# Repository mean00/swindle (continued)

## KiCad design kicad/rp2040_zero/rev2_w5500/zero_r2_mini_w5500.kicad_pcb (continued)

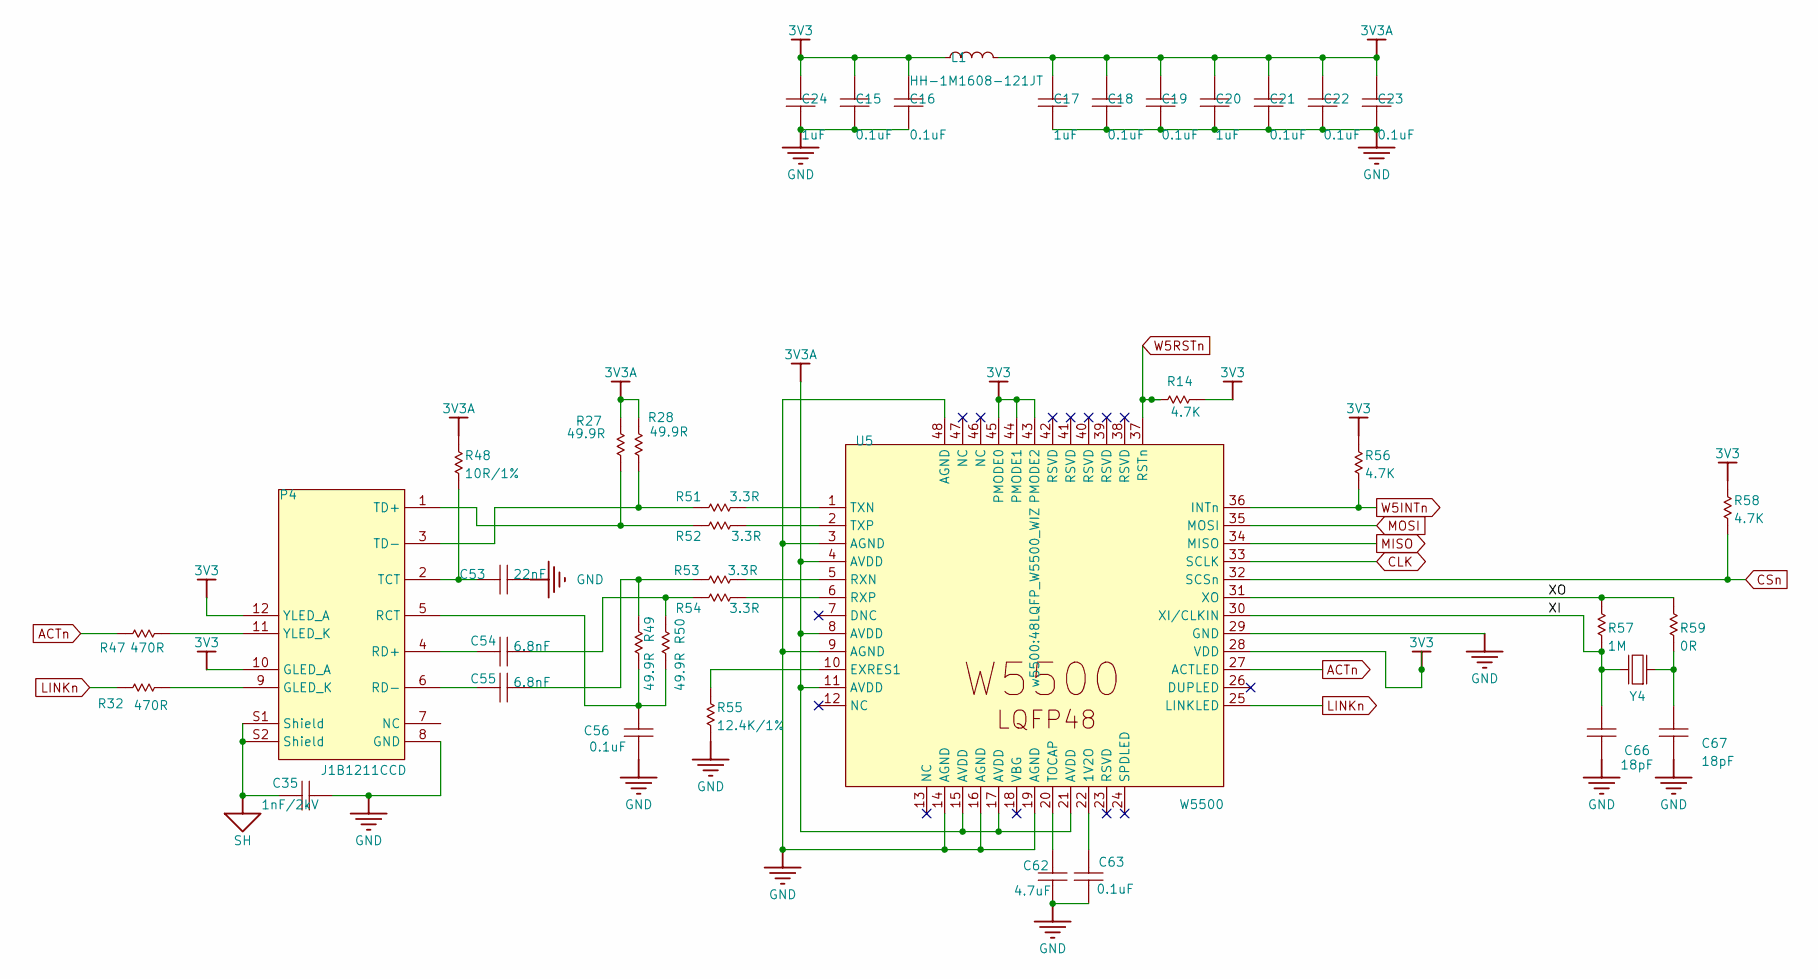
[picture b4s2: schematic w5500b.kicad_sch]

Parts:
C15, C16, C18, C19, C21, C22, C23, C56, C63: 0.1uF; C_0603_1608Metric
C17, C20, C24: 1uF; C_0603_1608Metric
C35: 1nF/2kV; C_0603_1608Metric
C53: 22nF; C_0603_1608Metric
C54, C55: 6.8nF; C_0603_1608Metric
C62: 4.7uF; C_0603_1608Metric
C66, C67: 18pF; C_0603_1608Metric
L1: HH-1M1608-121JT; L_0603_1608Metric
P4: J1B1211CCD; RJ45_Hanrun_HR911105A_Horizontal
R14, R56, R58: 4.7K; R_0603_1608Metric
R27, R28, R49, R50: 49.9R; R_0603_1608Metric
R32, R47: 470R; R_0603_1608Metric
R48: 10R/1%; R_0603_1608Metric
R51, R52, R53, R54: 3.3R; R_0603_1608Metric
R55: 12.4K/1%; R_0603_1608Metric
R57: 1M; R_0603_1608Metric
R59: 0R; R_0603_1608Metric
U5: W5500; 48LQFP_W5500_WIZ
Y4: 25MHz; Crystal_SMD_TXC_7M-4Pin_3.2x2.5mm

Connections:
3V3A: C17.2, C18.2, C19.2, C20.2, C21.2, C22.2, C23.2, L1.2, R27.2, R28.2, R48.1, U5.4 (AVDD), U5.8 (AVDD), U5.11 (AVDD), U5.15 (AVDD), U5.17 (AVDD), U5.21 (AVDD)
+3.3V: C15.2, C16.2, C24.2, L1.1, P4.10 (GLED_A), P4.12 (YLED_A), R14.2, R56.1, R58.1, U5.28 (VDD), U5.43 (PMODE2), U5.44 (PMODE1), U5.45 (PMODE0); also elsewhere on the board
/w5500b/XI: C66.2, R57.1, U5.30 (XI/CLKIN), Y4.1 (inp)
/w5500b/XO: R57.2, R59.2, U5.31 (XO)
ACTn: R47.1, U5.27 (ACTLED)
CLK: U5.33 (SCLK); also elsewhere on the board
CSn: R58.2, U5.32 (SCSn); also elsewhere on the board
GND: C15.1, C16.1, C17.1, C18.1, C19.1, C20.1, C21.1, C22.1, C23.1, C24.1, C35.1, C53.1, C56.1, C62.1, C63.1, C66.1, C67.1, P4.8 (GND), R55.2, U5.3 (AGND), U5.9 (AGND), U5.14 (AGND), U5.16 (AGND), U5.19 (AGND), U5.29 (GND), U5.48 (AGND); also elsewhere on the board
LINKn: R32.1, U5.25 (LINKLED)
MISO: U5.34 (MISO); also elsewhere on the board
MOSI: U5.35 (MOSI); also elsewhere on the board
unnamed: C54.1, R50.2, R54.1
unnamed: C55.1, R49.2, R53.1
unnamed: P4.9 (GLED_K), R32.2
unnamed: C56.2, P4.5 (RCT), R49.1, R50.1
unnamed: C54.2, P4.4 (RD+)
unnamed: C55.2, P4.6 (RD-)
unnamed: C53.2, P4.2 (TCT), R48.2
unnamed: P4.1 (TD+), R27.1, R52.1
unnamed: P4.3 (TD-), R28.1, R51.1
unnamed: P4.11 (YLED_K), R47.2
unnamed: C63.2, U5.22 (1V2O)
unnamed: R55.1, U5.10 (EXRES1)
unnamed: R53.2, U5.5 (RXN)
unnamed: R54.2, U5.6 (RXP)
unnamed: C62.2, U5.20 (TOCAP)
unnamed: R51.2, U5.1 (TXN)
unnamed: R52.2, U5.2 (TXP)
unnamed: C67.2, R59.1, Y4.3 (out)
SH: C35.2, P4.S1 (Shield), P4.S2 (Shield), P4.SH
W5INTn: R56.2, U5.36 (INTn); also elsewhere on the board
W5RSTn: R14.1, U5.37 (RSTn); also elsewhere on the board

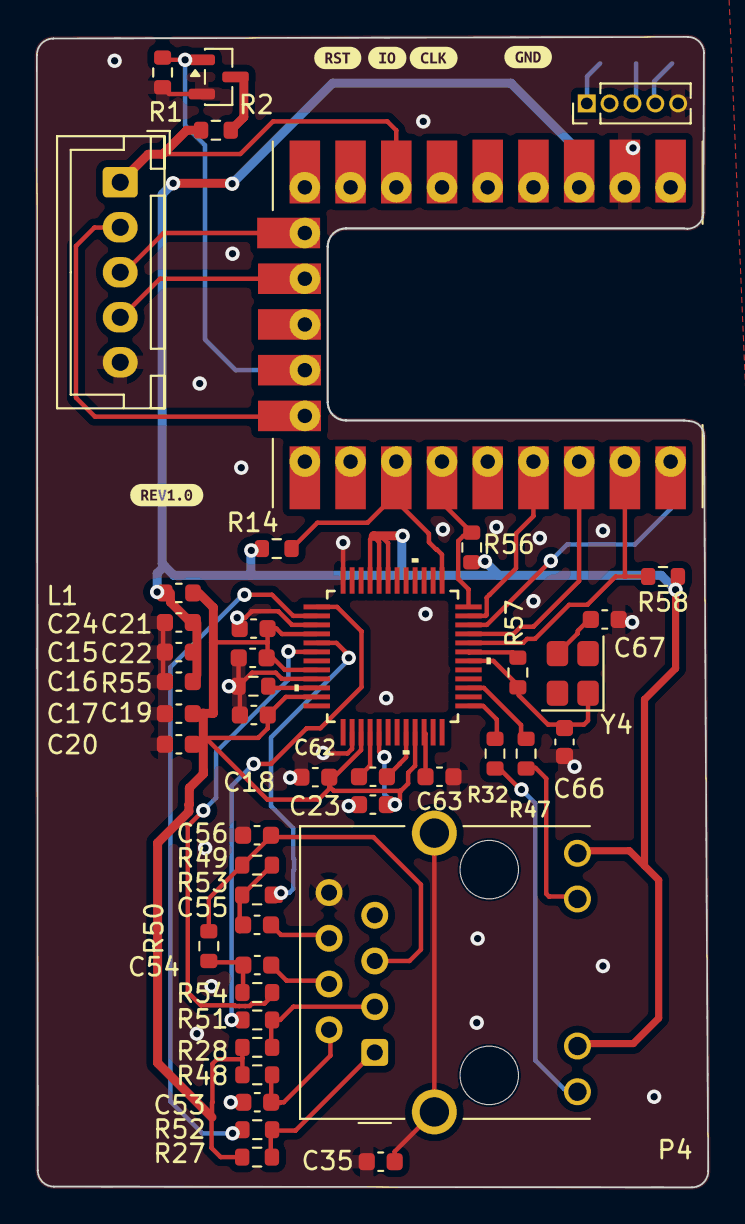
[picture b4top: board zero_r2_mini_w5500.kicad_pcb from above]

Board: 2 copper layers, 37.3 x 63.9 mm, 50 parts (0 on the bottom side), 38 nets.

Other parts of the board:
kibuzzard-6A66F7EE: G***; kibuzzard-6A66F7EE
kibuzzard-67D71CE3: G***; kibuzzard-67D71CE3
kibuzzard-67D71D2A: G***; kibuzzard-67D71D2A
kibuzzard-67D71D3A: G***; kibuzzard-67D71D3A
kibuzzard-67D71D53: G***; kibuzzard-67D71D53

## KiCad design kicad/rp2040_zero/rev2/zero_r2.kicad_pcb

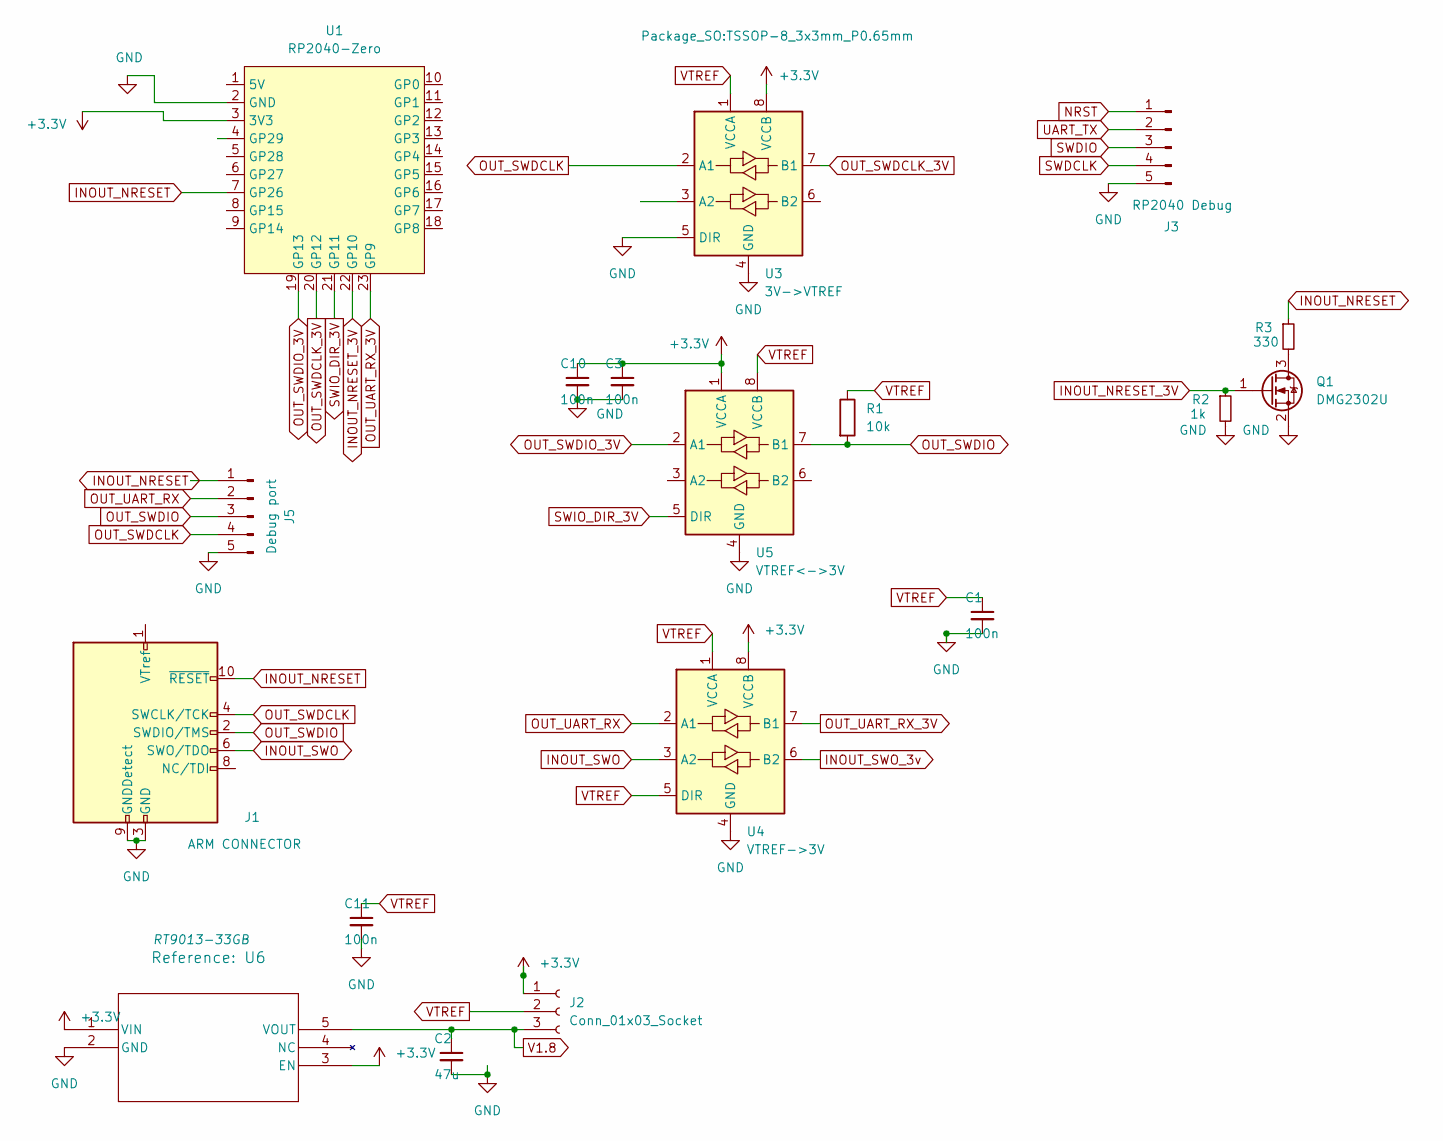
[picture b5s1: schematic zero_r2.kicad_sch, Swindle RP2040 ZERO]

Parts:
C1, C3, C10, C11: 100n; R_0603_1608Metric
C2: 47u; R_1210_3225Metric
J1: ARM CONNECTOR; PinHeader_2x05_P1.27mm_Vertical_SMD
J2: Conn_01x03_Socket; PinHeader_1x03_P2.54mm_Vertical
J3: RP2040 Debug; PinHeader_1x05_P1.00mm_Vertical
J5: Debug port; JST_XH_B5B-XH-A_1x05_P2.50mm_Vertical
Q1: DMG2302U; SOT-23
R1: 10k; R_0603_1608Metric
R2: 1k; R_0603_1608Metric
R3: 330; R_0603_1608Metric
U1: RP2040-Zero; RP2040 Zero
U3: 3V->VTREF; TSSOP-8_3x3mm_P0.65mm
U4: VTREF->3V; TSSOP-8_3x3mm_P0.65mm
U5: VTREF<->3V; TSSOP-8_3x3mm_P0.65mm
U6: RT9013-33GB; SOT-23-5_HandSoldering

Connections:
+3.3V: C3.1, C10.1, J2.1, U1.3 (3V3), U3.8 (VCCB), U4.8 (VCCB), U5.1 (VCCA), U6.1 (VIN), U6.3 (EN)
GND: C1.2, C2.2, C3.2, C10.2, C11.2, J1.3 (GND), J1.5 (GND), J1.9 (GNDDetect), J3.5, J5.5, Q1.2 (S), R2.2, U1.2 (GND), U3.4 (GND), U3.5 (DIR), U4.4 (GND), U5.4 (GND), U6.2 (GND)
INOUT_NRESET: J1.10 (~RESET), J5.1, R3.1, U1.7 (GP26)
INOUT_NRESET_3V: Q1.1 (G), R2.1, U1.22 (GP10)
INOUT_SWO: J1.6 (SWO/TDO), U4.3 (A2)
INOUT_SWO_3v: U4.6 (B2)
NRST: J3.1
unnamed: Q1.3 (D), R3.2
OUT_SWDCLK: J1.4 (SWCLK/TCK), J5.4, U3.2 (A1)
OUT_SWDCLK_3V: U1.20 (GP12), U3.7 (B1)
OUT_SWDIO: J1.2 (SWDIO/TMS), J5.3, R1.2, U5.7 (B1)
OUT_SWDIO_3V: U1.19 (GP13), U5.2 (A1)
OUT_UART_RX: J5.2, U4.2 (A1)
OUT_UART_RX_3V: U1.23 (GP9), U4.7 (B1)
SWDCLK: J3.4
SWDIO: J3.3
SWIO_DIR_3V: U1.21 (GP11), U5.5 (DIR)
UART_TX: J3.2
V1.8: C2.1, J2.3, U6.5 (VOUT)
VTREF: C1.1, C11.1, J2.2, R1.1, U3.1 (VCCA), U4.1 (VCCA), U4.5 (DIR), U5.8 (VCCB)

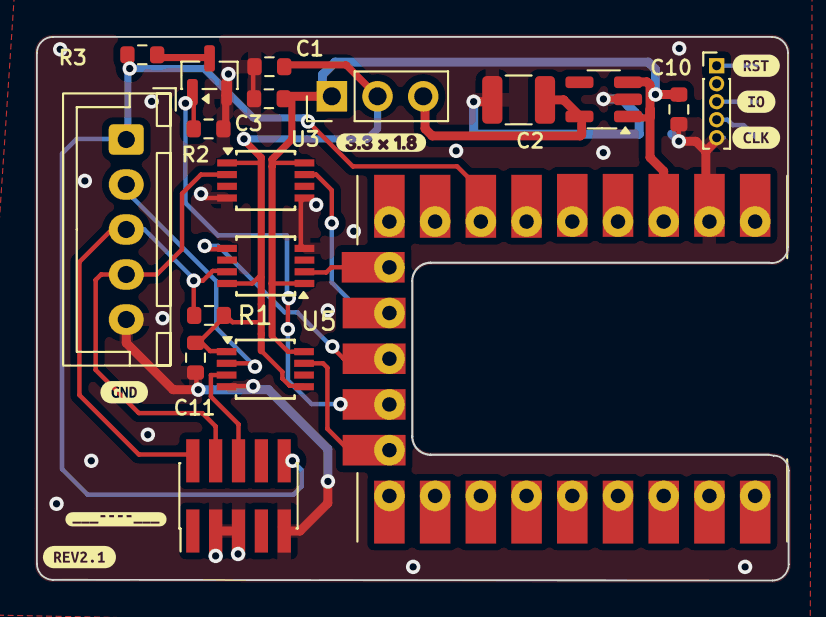
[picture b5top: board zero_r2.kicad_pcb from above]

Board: 2 copper layers, 41.8 x 30.2 mm, 26 parts (1 on the bottom side), 15 nets.

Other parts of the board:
kibuzzard-6A64D073: G***; kibuzzard-6A64D073
kibuzzard-6A64D231: G***; kibuzzard-6A64D231
kibuzzard-67D71CE3: G***; kibuzzard-67D71CE3
kibuzzard-67D71D2A: G***; kibuzzard-67D71D2A
kibuzzard-67D71D3A: G***; kibuzzard-67D71D3A
kibuzzard-67D71D53: G***; kibuzzard-67D71D53
kibuzzard-6714FCCA: G***; kibuzzard-6714FCCA
kibuzzard-6719D703: G***; kibuzzard-6719D703

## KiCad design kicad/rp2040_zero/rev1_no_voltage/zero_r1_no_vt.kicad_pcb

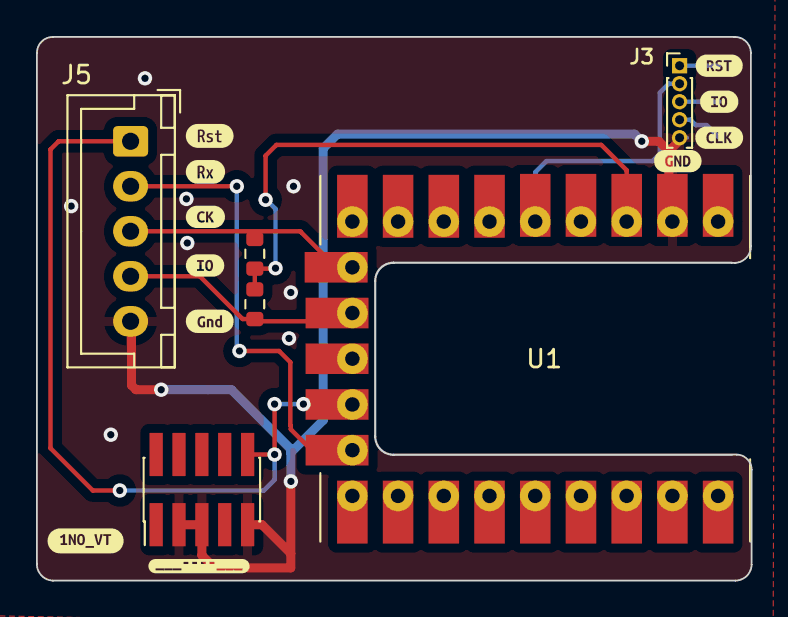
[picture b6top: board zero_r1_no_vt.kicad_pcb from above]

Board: 2 copper layers, 39.7 x 30.2 mm, 17 parts (0 on the bottom side), 7 nets.

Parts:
J1: jtag; PinHeader_2x05_P1.27mm_Vertical_SMD
J3: Debug port; PinHeader_1x05_P1.00mm_Vertical
J5: Debug port; JST_XH_B5B-XH-A_1x05_P2.50mm_Vertical
PULLUP, PULLUP2: R_0603_1608Metric
U1: RP2040-Zero; RP2040 Zero
kibuzzard-67A3B7A3: G***; kibuzzard-67A3B7A3
kibuzzard-67D71CE3: G***; kibuzzard-67D71CE3
kibuzzard-67D71D2A: G***; kibuzzard-67D71D2A
kibuzzard-67D71D3A: G***; kibuzzard-67D71D3A
kibuzzard-67D71D53: G***; kibuzzard-67D71D53
kibuzzard-67D71DD3: G***; kibuzzard-67D71DD3
kibuzzard-67D71DDE: G***; kibuzzard-67D71DDE
kibuzzard-67E96C07: G***; kibuzzard-67E96C07
kibuzzard-6719D703: G***; kibuzzard-6719D703
kibuzzard-67310D89: G***; kibuzzard-67310D89
kibuzzard-67310DA4: G***; kibuzzard-67310DA4

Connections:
+3.3V: PULLUP.2, PULLUP2.2, U1.3 (3V3)
GND: J1.3 (GND), J1.5 (GND), J1.9 (GNDDetect), J3.5, J5.5, U1.2 (GND)
INOUT_NRESET: J1.10 (~RESET), J5.1, U1.7 (GP26), U1.22 (GP10)
OUT_SWDCLK_3V: J5.4, PULLUP2.1, U1.20 (GP12)
OUT_SWDIO_3V: J5.3, PULLUP.1, U1.19 (GP13)
OUT_UART_RX_3V: J5.2, U1.23 (GP9)
UART_TX: J3.2, U1.5 (GP28)

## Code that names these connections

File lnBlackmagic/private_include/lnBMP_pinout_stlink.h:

#pragma once
const lnPin _mapping[8] = {
    PA0, // 0 TMS_PIN
    PA0, // 1 TDI_PIN
    PA0, // 2 TDO_PIN
    PA0, // 3 TCK_PIN
    PA0, // 4 TRACESWO_PIN

    PA13, // 5 SWDIO_PIN
    PA14, // 6 SWCLK_PIN

    PB4, // 7 RST
};

#define PIN_ADC_NRESET_DIV_BY_TWO PA3 // this pins is connected to NRST/2
#define PIN_ADC_NRESET_MULTIPLIER 1.  // 2.0 if divided by 2 , 1.0 if not divided

#define LN_USB_INSTANCE         1
#define LN_SERIAL_INSTANCE      0

#define EXTRA_SETUP() { extern void lnExtiNoSWD();   lnPinMode(PA9, lnOUTPUT);    lnPinMode(PA10, lnOUTPUT);    lnPinMode(PB6, lnALTERNATE_PP);    lnPinMode(PB7, lnALTERNATE_PP);lnExtiNoSWD();}

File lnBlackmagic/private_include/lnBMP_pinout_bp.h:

#pragma once
#define BM_NB_PINS 7
// mapping of BMP gpio to the GPIO we use

#ifdef USE_STLINK_PINOUT
const lnPin _mapping[8] = {
    PA0, // 0 TMS_PIN
    PA0, // 1 TDI_PIN
    PA0, // 2 TDO_PIN
    PA0, // 3 TCK_PIN
    PA0, // 4 TRACESWO_PIN

    PA13, // 5 SWDIO_PIN
    PA14, // 6 SWCLK_PIN

    PB4, // 7 RST
};
#else

const lnPin _mapping[8] = {
    PA0, // 0 TMS_PIN
    PA0, // 1 TDI_PIN
    PA0, // 2 TDO_PIN
    PA0, // 3 TCK_PIN
    PA0, // 4 TRACESWO_PIN

    PB8, // 5 SWDIO_PIN
    PB9, // 6 SWCLK_PIN

    PB6, // 7 RST
};

#endif
enum lnBMPPins
{
    TTMS_PIN = 0,
    TTDI_PIN = 1,
    TTDO_PIN = 2,
    TTCK_PIN = 3,
    TTRACE_PIN = 4,
    TSWDIO_PIN = 5,
    TSWDCK_PIN = 6,
    TRESET_PIN = 7,
};

#define PIN_ADC_NRESET_DIV_BY_TWO PA3 // this pins is connected to NRST/2
#define PIN_ADC_NRESET_MULTIPLIER 1.  // 2.0 if divided by 2 , 1.0 if not divided

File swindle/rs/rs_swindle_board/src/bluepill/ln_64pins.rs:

// GD32F303 / CH32V307 probe, 64 pins package (CMake: `USE_64PIN_PACKAGE`).
//
// Same debug header wiring as the 48 pins package; the target voltage is sensed
// on PA4 here, PA3 there.

use crate::board_desc::Board;
use crate::pins::{pa, pb, pc};

pub const BOARD: Board = Board {
    name: "ln_64pins",
    dev: [
        pa(0), // 0 TMS
        pa(0), // 1 TDI
        pa(0), // 2 TDO
        pa(0), // 3 TCK
        pa(0), // 4 TRACESWO
        pb(8), // 5 SWDIO
        pb(9), // 6 SWCLK
        pb(6), // 7 RST
        pc(3), // 8 DIRECTION (level shifter)
    ],
    adc_nreset: Some(pa(4)), // NRST/2 divider
    adc_multiplier: 1.0,
    // The bridge / log UART pins of this platform are owned by the esprit UART
    // driver (`rs_uart_bluepill`, instance -> pin), not by the board table.
    uart_rx: None,
    uart_tx: None,
    usb_gdb: 1,
    usb_serial: 2,
    usb_logger: 2,
    leds: &[pc(13), pa(8), pb(13)],
    ws2812: Some(pb(4)),
};

// The bluepill compatible `lnPin` encoding, as esprit spells it: PA0..PA15 = 0..15,
// PB0..PB15 = 16..31, PC0..PC15 = 32..47. A wrong helper would silently move the
// debug pins, so pin a few down.
const _: () = {
    assert!(pb(0) == 16);
    assert!(pb(8) == 24);
    assert!(pc(3) == 35);
    assert!(BOARD.dev[5] == pb(8)); // SWDIO
    assert!(BOARD.dev[6] == pb(9)); // SWCLK
    assert!(BOARD.dev[7] == pb(6)); // RST
    assert!(BOARD.dev[8] == pc(3)); // DIRECTION
};

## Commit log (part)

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2025-12-22 patch : remove doubly defined warning about rvswd
2025-12-22 [lldb] Try to be nicer with lldb
2025-12-22 ch32 : add preliminary support for CH32V208
2025-12-22 ch32 stub : fixup relative paths
2025-12-22 hosted: update to new net API+ handle disconnect
2025-12-22 when using ch32v208, switch to 25Mhz crystal
2025-12-22 ch32: check if the chip has hw breakpoint before engaging sw breakpoint
2025-12-22 misc: move flashstub close to the target
2025-12-22 register: dont skip the first byte (temptative), that makes mcause work again
2025-12-22 change esprit branch
2025-12-22 hosted: begin to fix qt6 based fast event group + hacked qt network double check threading better threading management
2025-12-22 swindle: fix mon redirect to usb
2025-12-22 net:use shared eventgroup for gdb (and later rtt/ serial) native multi socket implementation ,add gdb+rtt (It can sort of deadlock)
2025-12-22 use lnSocket API
2025-12-22 flashstub: for ch32vxx build with no hw fpu so it works with ch32v2xx also
2025-12-22 ch32: revert toolchain for clang 19.1
2025-12-22 fix usb vs net builds
2025-12-22 usb: make usb optional, prepare for eth
2025-12-22 begin adding lwip
2025-12-22 vscode: general update
2025-12-22 mcu/Eth: update memory layout for ch32v307 + ethernet more ethernet swindle fix pin configuration at connect/disconnect tune build, remove LPC to get some room riscv: update gcc toolchain update ethe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
2025-12-22 basic connection to rng stub
2025-12-22 bmp : abort on first write error (buffered)
2025-12-22 rvtaps: oops, do the memset after having check the buffer is valid
2025-12-22 ch32v23: optional verbosity in the driver
2025-12-22 patch : newer version of stop when flash error happens
2025-12-28 update esprit
2025-12-28 usb<->uart : small optimization + check
2025-12-28 rtt: some fixes, thanks G
2025-12-28 kicad: update to v9
2025-12-29 bump version to 600
2025-12-30 make swindle.rs usable by rust also
2025-12-30 rs: std/no_std compatibility
2025-12-31 esp32: fix up cmake list
2026-01-08 sync with esprit
2026-01-09 rust: propagate feature to rust_esprit
2026-01-17 restructure the MCU dependant part to simplify so that we have dedicated swd/rvswd function for STM/WCH/GD, RP2040 and ESP ESP is not working
2026-01-18 swd: cleanup turnaround
2026-01-18 ln: swdio read fixup
2026-01-18 swd/rp2040: small optimization
2026-01-23 Cleanup IO, make a template and use input / output / OD for esp
2026-01-23 split usb/usb instances from pinout and deal with pinout through swindleio (incomplete)
2026-01-24 use template for ln gpio, with a macro for input output add an extra wait period The RP2040 is off by one cycle, not really sure why
2026-01-24 esp32: put bitbanging code in IRAM
2026-01-25 armv8m: properly handle faults
2026-01-25 58 vs 64 pins has been moved to the right subfolder
2026-01-25 fix swd template
2026-01-25 rp2040: use swd template, adapt PIO accordingly
2026-01-26 swd: de-optimize it a bit
2026-01-26 esprit remove hardlink
2026-01-26 restore esprit as submodule
2026-01-26 rust : add workspace
2026-01-26 cargo.toml cleanup
2026-01-26 rust: cleanup
2026-01-27 update esprit and default
2026-01-27 rename rvswd template
2026-01-30 shuffle files around to have cleaner source tree
2026-01-31 esp32: fixup gpio, add dimmy spi
2026-02-01 CH32Vxx: Recompile the flashstub using a nicer cmake based project
2026-02-01 ch32: add new flashstub
2026-02-03 rtt: only stop to read rtt info if we must
2026-02-03 bmp: add the export arch patch
2026-02-05 rp2040: rvswd simplification
2026-02-05 rtt/arch: retrieve the arch to know if rtt needs halting the MCU
2026-02-07 add preliminary CMakePreset
2026-02-08 cleanup ufmt crate, avoid double promotion, limit embedded printf The goal is really to avoid indirectly call some double function and pull the double math
2026-02-08 ch32: fix flash size
2026-02-08 rust: use our modified gdb_print! to reduce footprint
2026-02-08 kicad: cosmetic
2026-02-09 fix the 30kB size increase
2026-02-09 fix bootloader size
2026-02-10 helper script
2026-02-10 fold direction control into direction pin
2026-02-11 clippify bmplogger
2026-02-12 update ci script to use presets
2026-02-14 update patches
2026-02-14 add fastgpio
2026-02-14 rust: try to make rsbmp a normal rust crate
2026-02-15 esp32s3: fixup fastio
2026-02-15 esp: force -O3 for bitbanging
2026-02-15 esp : fixup frequency set/get
2026-02-16 host: fixup logic with rsbmp wrapper
2026-02-17 rust: update cargo deps
2026-02-26 rename
2026-03-07 update blackmagic
2026-03-07 esp: renable redirect swd functions
2026-03-07 esprit : move to master
2026-03-17 esp32: merge pinout
2026-03-17 esp: split board pinout between normal and mini
2026-03-20 swd: switch to input when we read
2026-03-20 esp: change ESP mini pinout
2026-03-22 esp: add direct ADC call
2026-03-22 esp: wroom ADC is on GPIO4
2026-03-22 updat esprit
2026-03-25 update kicad
2026-03-25 add devpod.sh
2026-03-31 hosted: fix infinite loop in DMI read/write retry logic
2026-04-19 udev: update & and fix udev rules
2026-05-07 update devpod and start fixing tests
2026-05-08 rp2350: update esprit , add preset
2026-05-08 gitignore
2026-05-08 switch blackmagic to codeberg
2026-05-14 rust: cleanup and move CDCs to rust
2026-05-14 move CDC to the rust side
2026-05-14 update esprit , add RP2350 preset
2026-05-14 fix hosted+clang
2026-05-14 freertos: fixup task decoding, using the helper structure if presetn freertos: fixup the parsing when switching
2026-05-14 update esprit & switch blackmagic to codeberg
2026-05-14 berg
2026-05-15 general cleanup (hosted)
2026-05-15 freertos: fixup
2026-05-15 freertos: add a default thread name
2026-05-15 cmake lint
2026-05-15 build RP2350 in ci
2026-05-15 attempt at rebasing to current BMP code
2026-05-15 devpod
2026-05-30 minor cleanup
2026-05-31 Redo the RPC architecture to be autogenerated from a toml file
2026-05-31 prettify some gdb_print
2026-05-31 increase static SRAM for CH32xx
2026-06-02 Remove dead code, reorganize, clippy fixes
2026-06-03 Split more cleanly between hosted and native builds by moving code to two disting submodules
2026-06-05 use smaller start_by command structure switch from hashbrown to heapless::LinearMap freertos: remove hardcoded value freertos: put back default for freertos offsets freertos: switch back and forth + 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
2026-06-06 freertos: cache TCB freertos : fix task switching again increase static ram freertos: check return value of mem read/mem write and propagate
2026-06-06 update logging system, use esprit::logger! rather than gdb_out else it might interact with gdb at the wrong spot and cause issues
2026-06-06 hosted: cleanup, add comments
2026-06-07 update blackmagic + fix rtt no_stop mode
2026-06-22 when detaching, reset the gpio to write mode in case it did a THROW in read mode
2026-06-24 swindle : inline init of autoauto to avoid copies swindle : optimize a bit
2026-06-24 update doxygen comments
2026-06-24 rpc: avoid allocating 1k on the stack rpc: add bmp_gpio_reset
2026-06-28 rename + cleanup+ factorize some rp2040 code
2026-06-28 changed led color depending on network state
2026-06-28 W5500+rp2040: derive mac address from board serial id
2026-06-28 cleanup build, fix w5500 vs network
2026-06-28 tune naming
2026-06-28 update comments
2026-06-30 proper reinit of RP2040 pins
2026-06-30 rtt: simplify can_stop, no need for that many unsafe
2026-06-30 update ci run
2026-06-30 gdbstub: fix off by one + missing overflow check
